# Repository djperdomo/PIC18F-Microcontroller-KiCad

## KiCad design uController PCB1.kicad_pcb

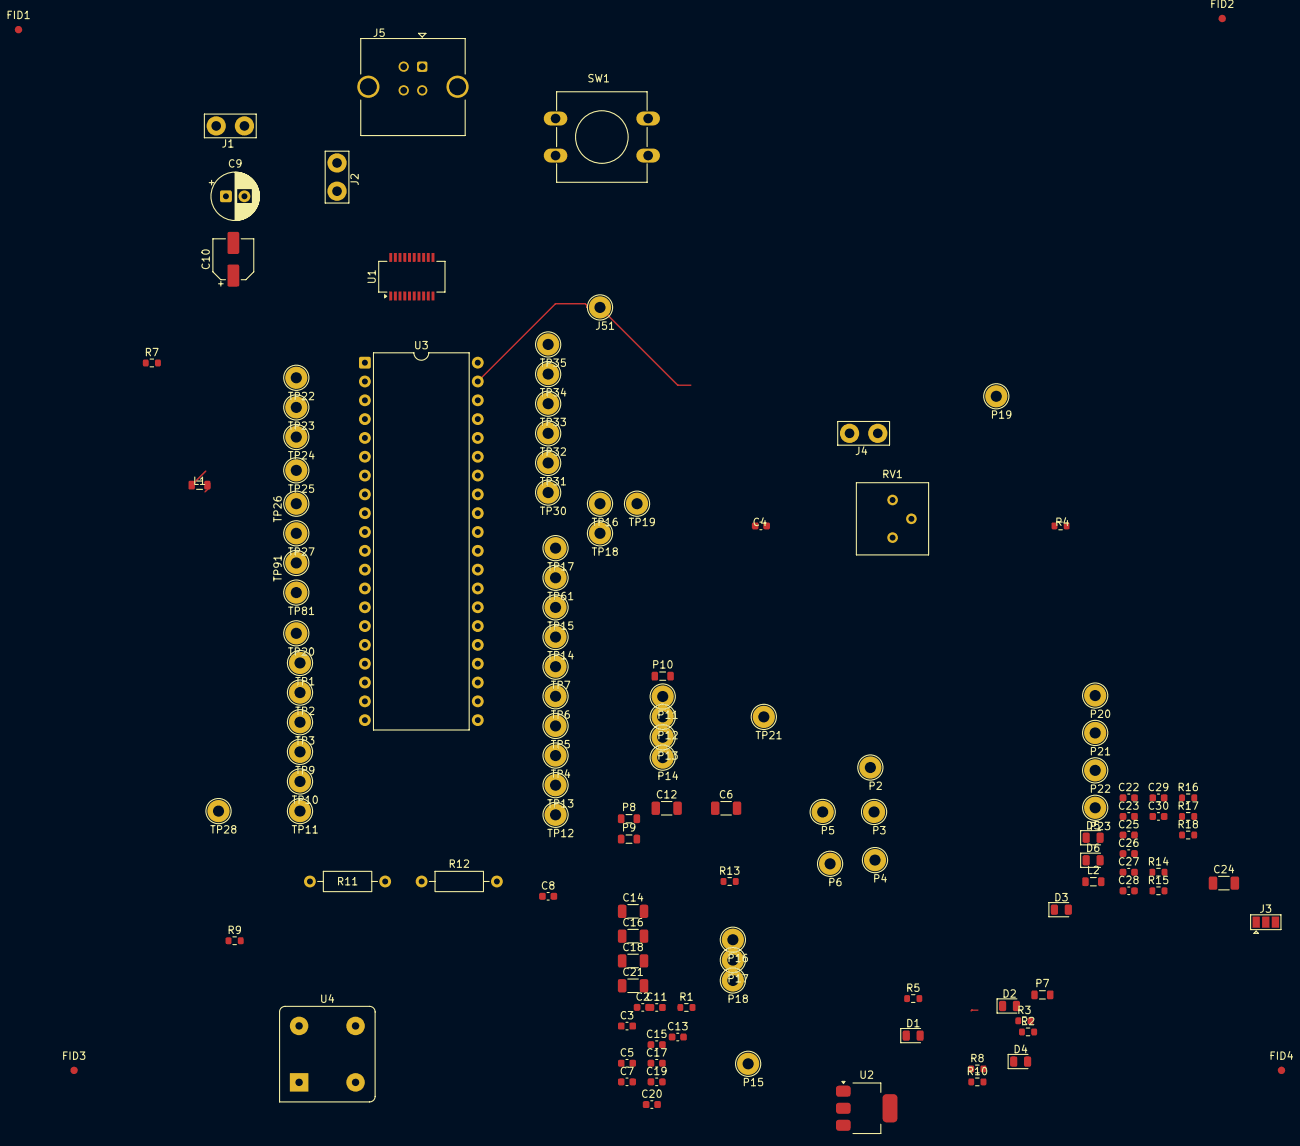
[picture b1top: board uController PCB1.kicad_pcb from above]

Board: 2 copper layers, 128 parts (0 on the bottom side), 63 nets.

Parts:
C2, C3, C25, C27: 47pF; C_0603_1608Metric
C4, C5, C7, C8, C11, C13, C15, C17, C19, C20, C22, C23, C26, C28, C29, C30: 0.1uF; C_0603_1608Metric
C6, C12, C14, C16, C18, C21, C24: 10uF; C_1206_3216Metric
C9: 100uF; CP_Radial_D6.3mm_P2.50mm
C10: 22uF; CP_Elec_5x5.4
D1, D2, D3, D4, D5, D6: LED; LED_0805_2012Metric
FID1, FID2, FID3, FID4: Fiducial; Fiducial_1mm_Mask2mm
J1: SCREWTERM; TestPoint_Bridge_Pitch3.81mm_Drill1.3mm
J2, J4: JUMPER2; TestPoint_Bridge_Pitch3.81mm_Drill1.3mm
J3: JUMPER3; SolderJumper-3_P1.3mm_Open_Pad1.0x1.5mm
J5: USB_B; USB_B_TE_5787834_Vertical
J51: Conn_01x06_Pin; TestPoint_Loop_D2.54mm_Drill1.5mm_Beaded
L1, L2: FerriteBead; L_0805_2012Metric
P2, P3, P4, P5, P6, P11, P12, P13, P14, P15, P16, P17, P20, P21, P22, P23: Conn_01x01_Pin; TestPoint_Loop_D2.54mm_Drill1.5mm_Beaded
P7, P8, P9, P10: Conn_01x01_Pin; L_0805_2012Metric
P18, P19: TestPoint_Loop_D2.54mm_Drill1.5mm_Beaded
R1, R2, R14, R16: 27; R_0603_1608Metric
R3, R7, R15: 10k; R_0603_1608Metric
R4, R5, R17, R18: 180; R_0603_1608Metric
R8, R10, R13: 402; R_0603_1608Metric
R9: 10K; R_0603_1608Metric
R11, R12: 4.7K; R_Axial_DIN0207_L6.3mm_D2.5mm_P10.16mm_Horizontal
RV1: R_Potentiometer; Potentiometer_Bourns_3386P_Vertical
SW1: SW KEY-SPST; SW_PUSH-12mm
TP1, TP2, TP3, TP4, TP5, TP6, TP7, TP9, TP10, TP11, TP12, TP13, TP14, TP15, TP16, TP17, TP18, TP19, TP20, TP21, TP22, TP23, TP24, TP25, TP26, TP27, TP28, TP30, TP31, TP32, TP33, TP34, TP35, TP61, TP81, TP91: TestPoint_Loop_D2.54mm_Drill1.5mm_Beaded
U1: FT231XS; SSOP-20_3.9x8.7mm_P0.635mm
U2: LD1117S33TR_SOT223; SOT-223-3_TabPin2
U3: PIC18F4550-IP; DIP-40_W15.24mm
U4: CXO_DIP8; Oscillator_DIP-8_LargePads

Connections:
+3.3V: C20.1, J3.1 (A), R9.2, U2.2 (VO), U4.8 (Vcc)
/RB3: R8.1, TP33.1 (1_1), U3.36 (RB3/AN9/CCP2/VPO)
/RX: TP6.1 (1_1), U3.25 (TX/CK/RC6)
/SCL: R11.1, TP31.1 (1_1), U3.34 (RB1/AN10/INT1/SCK/SCL)
/SDA: R12.1, TP30.1 (1_1), U3.33 (RB0/AN12/INT0/FLT0/SDI/SDA)
/TX: TP7.1 (1_1), U3.26 (SDO/RX/DT/RC7)
/USB_RST: R3.2, R15.2, U1.14 (~RESET)
/clk: U3.13 (OSC1/CLKI), U4.5 (OUT)
GND: C2.2, C3.2, C4.2, C5.2, C6.2, C7.2, C8.2, C9.2, C10.2, C11.2, C12.2, C13.2, C14.2, C15.2, C16.2, C17.2, C18.2, C19.2, C20.2, C22.2, C23.2, C24.2, C25.2, C26.2, C27.2, C28.2, C29.2, C30.2, D3.1 (K), D4.1 (K), J1.1 (A_1), J5.4 (GND), J5.SH (Shield), P2.1 (Pin_1_1), P4.1 (Pin_1_1), P6.1 (Pin_1_1), P11.1 (Pin_1_1), P12.1 (Pin_1_1), P13.1 (Pin_1_1), P14.1 (Pin_1_1), P16.1 (Pin_1_1), P17.1 (Pin_1_1), P19.1 (1_1), R11.2, R12.2, RV1.3, TP18.1 (1_1), TP21.1 (1_1), U1.6 (GND), U1.16 (GND), U2.1 (GND), U3.12 (VSS), U3.31 (VSS), U4.4 (GND)
unnamed: C21.1, R13.2
unnamed: C21.2, P18.1 (1_1)
unnamed: C3.1, R2.1
unnamed: C2.1, R1.1
unnamed: D1.2 (A), R5.2
unnamed: D1.1 (K), U1.10 (CBUS2)
unnamed: D2.2 (A), R4.2
unnamed: D2.1 (K), U1.17 (CBUS1)
unnamed: D3.2 (A), R8.2
unnamed: D4.2 (A), R10.2
unnamed: D5.2 (A), R17.2
unnamed: D6.2 (A), R18.2
unnamed: C14.1, J3.3 (B)
unnamed: J4.1 (A_1), RV1.2
unnamed: TP22.1 (1_1), U3.2 (RA0/AN0)
unnamed: C27.1, J5.3 (D+), R14.1
unnamed: C25.1, J5.2 (D-), R16.1
unnamed: C23.1, J5.1 (VBUS), L2.2
unnamed: J51.1 (Pin_1_1), SW1.2 (B_2)
unnamed: P7.1 (Pin_1_1), U1.19 (CBUS3)
unnamed: P8.1 (Pin_1_1), U1.18 (CBUS0)
unnamed: P9.1 (Pin_1_1), U1.2 (~RTS)
unnamed: P10.1 (Pin_1_1), U1.9 (~CTS)
unnamed: R1.2, R16.2, U1.12 (USBDM)
unnamed: R2.2, R14.2, U1.11 (USBDP)
unnamed: C9.1, C15.1, U2.3 (VI)
unnamed: TP91.1 (1_1), U3.8 (CK1SPP/AN5/RE0)
unnamed: TP20.1 (1_1), U3.9 (CK2SPP/AN6/RE1)
unnamed: TP81.1 (1_1), U3.10 (OESPP/AN7/RE2)
unnamed: TP3.1 (1_1), U3.17 (P1A/CCP1/RC2)
unnamed: TP15.1 (1_1), U3.28 (P1B/SPP5/RD5)
unnamed: TP61.1 (1_1), U3.29 (P1C/SPP6/RD6)
unnamed: TP17.1 (1_1), U3.30 (P1D/SPP7/RD7)
unnamed: TP23.1 (1_1), U3.3 (RA1/AN1)
unnamed: R13.1, TP24.1 (1_1), U3.4 (RA2/AN2/Vref-/CVref)
unnamed: TP25.1 (1_1), U3.5 (RA3/AN3/Vref+)
unnamed: TP26.1 (1_1), U3.6 (RA4/T0CKI/C1OUT/RCV)
unnamed: TP27.1 (1_1), U3.7 (RA5/AN4/~SS/HLVDIN/C2OUT)
unnamed: TP32.1 (1_1), U3.35 (RB2/AN8/INT2/VMO)
unnamed: TP34.1 (1_1), U3.37 (RB4/AN11/KBI0/CSSPP)
unnamed: TP35.1 (1_1), U3.38 (RB5/KBI1/PGM)
unnamed: TP10.1 (1_1), U3.19 (SPP0/RD0)
unnamed: TP11.1 (1_1), U3.20 (SPP1/RD1)
unnamed: TP12.1 (1_1), U3.21 (SPP2/RD2)
unnamed: TP13.1 (1_1), U3.22 (SPP3/RD3)
unnamed: TP14.1 (1_1), U3.27 (SPP4/RD4)
unnamed: TP1.1 (1_1), U3.15 (T1OSO/T13CKI/RC0)
unnamed: TP4.1 (1_1), U3.23 (VM/D-/RC4)
unnamed: TP5.1 (1_1), U3.24 (VP/D+/RC5)
unnamed: TP9.1 (1_1), U3.18 (VUSB)
unnamed: R7.1, TP28.1 (1_1), U3.1 (Vpp/~MCLR/RE3)
unnamed: TP2.1 (1_1), U3.16 (~UOE/CCP2/T1OSI/RC1)
unnamed: R9.1, U4.1 (EN)
VCC: C4.1, C5.1, C6.1, C7.1, C8.1, C10.1, C11.1, C12.1, C13.1, C16.1, C17.1, C18.1, C19.1, C22.1, C24.1, C26.1, C28.1, C29.1, C30.1, J3.2 (C), L1.1, L2.1, P3.1 (Pin_1_1), P5.1 (Pin_1_1), P15.1 (Pin_1_1), R3.1, R4.1, R5.1, R7.2, R10.1, R15.1, R17.1, R18.1, RV1.1, TP16.1 (1_1), TP19.1 (1_1), U1.3 (VCCIO), U1.13 (3V3OUT), U1.15 (VCC), U3.11 (VDD), U3.32 (VDD)
